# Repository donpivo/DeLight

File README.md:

Description: https://retronics.no/2024/05/17/diy-work-light-warning-light-emergency-light-morse-sos-flasher-for-dewalt-xr-batteries/

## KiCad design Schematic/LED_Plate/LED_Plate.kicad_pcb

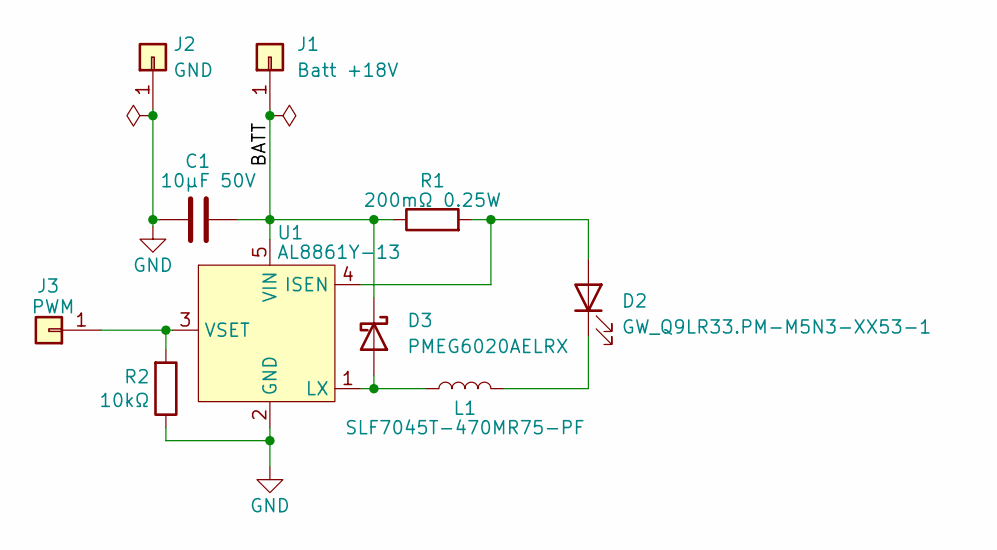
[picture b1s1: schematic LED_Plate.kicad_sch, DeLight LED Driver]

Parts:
C1: 10µF 50V; C_0805_2012Metric_Pad1.18x1.45mm_HandSolder
D2: GW_Q9LR33.PM-M5N3-XX53-1; LED_GW_Q9LR33.PM-M5N3-XX53-1
D3: PMEG6020AELRX; Nexperia_CFP3_SOD-123W
J1: Batt +18V; TestPoint_Pad_2.5x2.5mm
J2: GND; TestPoint_Pad_2.5x2.5mm
J3: PWM; TestPoint_Pad_2.5x2.5mm
L1: SLF7045T-470MR75-PF; SLF7032_7045
R1: 200mΩ 0.25W; R_1206_3216Metric_Pad1.30x1.75mm_HandSolder
R2: 10kΩ; R_0603_1608Metric_Pad0.98x0.95mm_HandSolder
U1: AL8861Y-13; SOT89-5

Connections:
/BATT: C1.2, D3.1 (K), J1.1, R1.1, U1.5 (VIN)
GND: C1.1, J2.1, R2.1, U1.2 (GND)
unnamed: D2.2 (A), R1.2, U1.4 (ISEN)
unnamed: D2.1 (K), L1.2
unnamed: D3.2 (A), L1.1, U1.1 (LX)
unnamed: J3.1, R2.2, U1.3 (VSET)

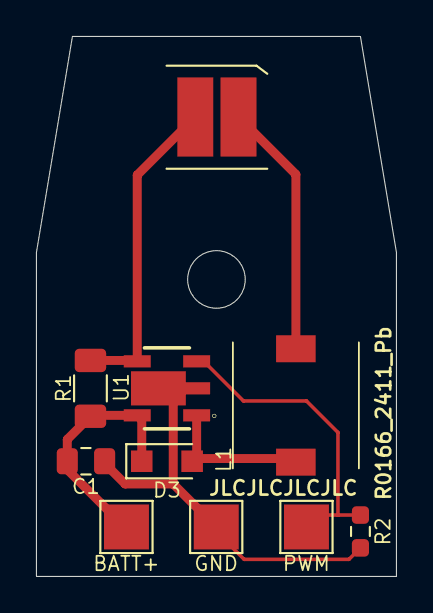
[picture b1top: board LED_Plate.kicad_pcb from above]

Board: 2 copper layers, 20.0 x 30.0 mm, 10 parts (0 on the bottom side), 6 nets.

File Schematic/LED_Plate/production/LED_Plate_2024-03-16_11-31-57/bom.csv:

Designator,Footprint,Quantity,Value,LCSC Part #
C1,0805,1,10µF,
D2,LED_GW_Q9LR33.PM-M5N3-XX53-1,1,LED,
D3,Nexperia_CFP3_SOD-123W,1,PMEG6020AELRX,
J1,TestPoint_Pad_2.5x2.5mm,1,Batt +18V,
J2,TestPoint_Pad_2.5x2.5mm,1,GND,
J3,TestPoint_Pad_2.5x2.5mm,1,PWM,
L1,SLF7032_7045,1,SLF7045T-470MR75-PF,
R1,1206,1,250mΩ 0.25W,
R2,0603,1,10kΩ,
U1,SOT89-5,1,AL8861Y-13,

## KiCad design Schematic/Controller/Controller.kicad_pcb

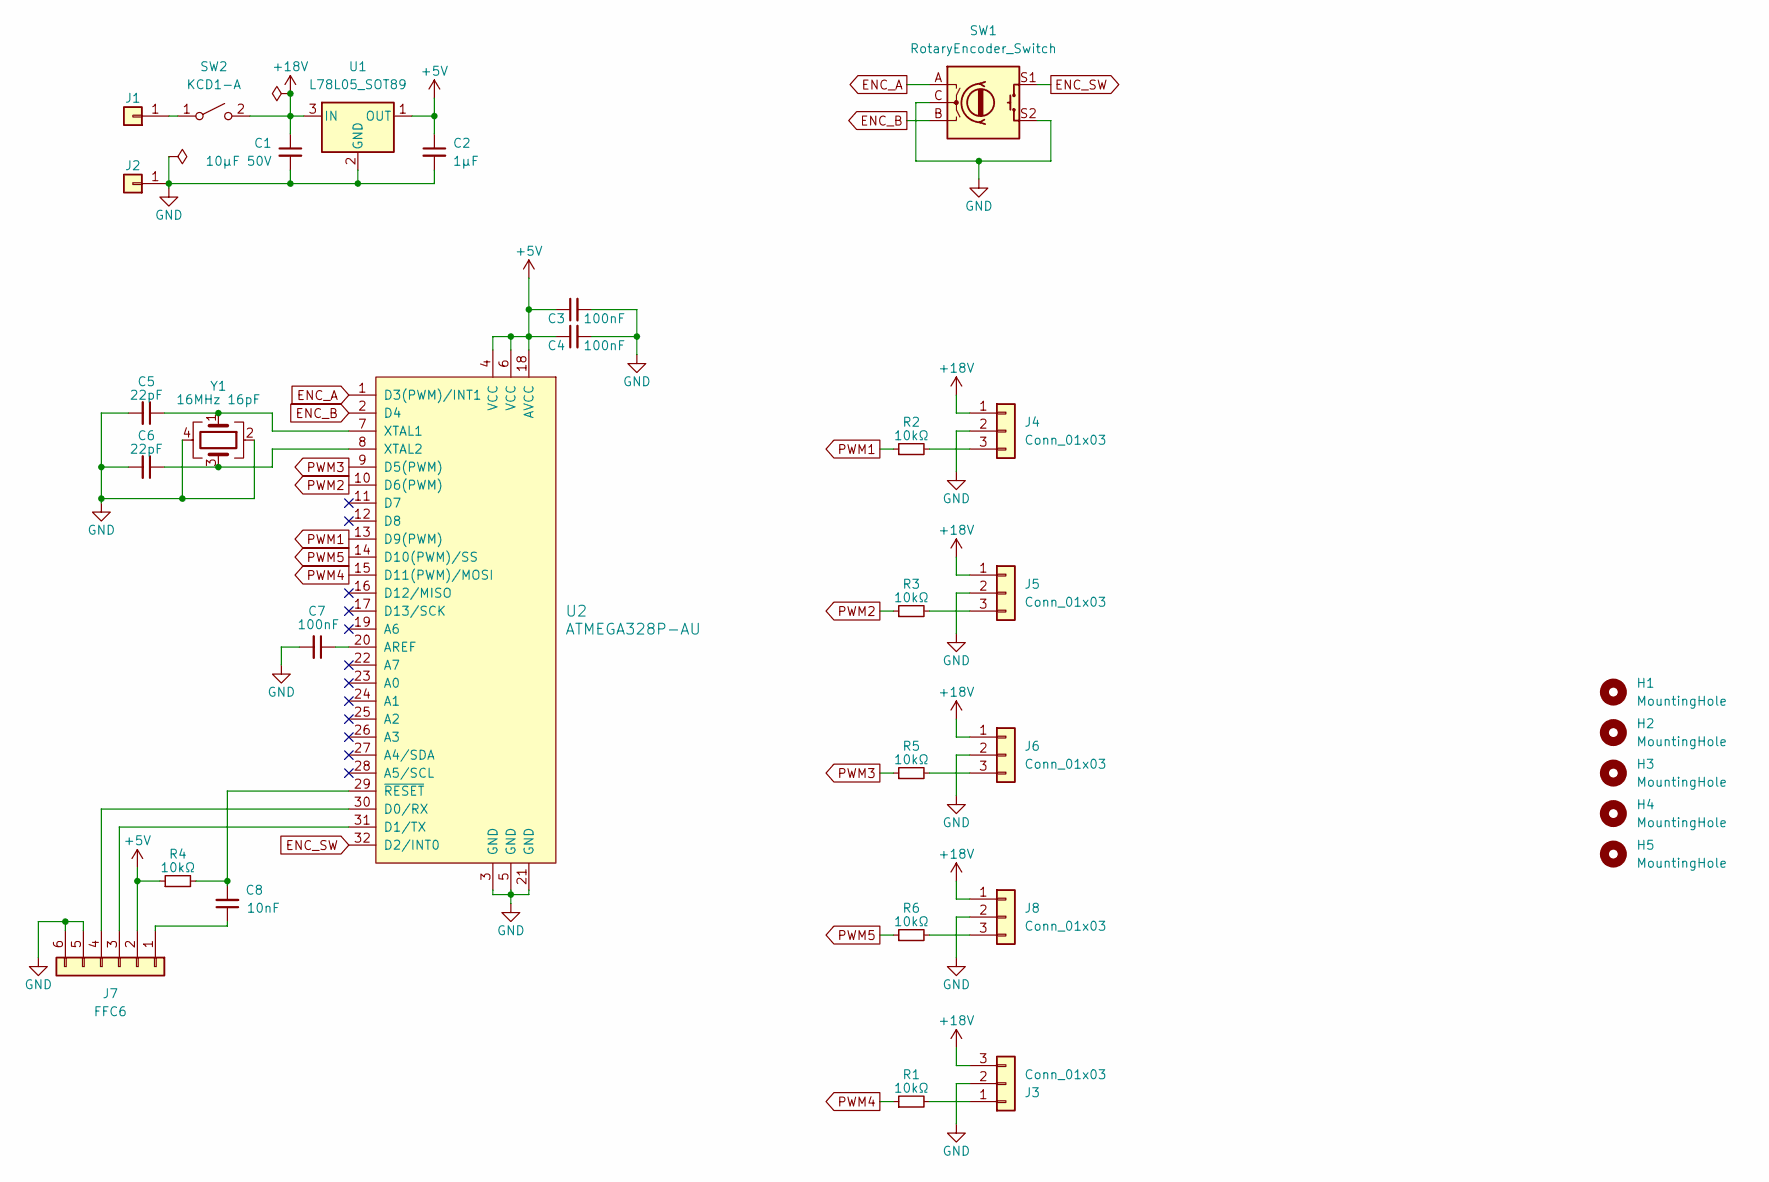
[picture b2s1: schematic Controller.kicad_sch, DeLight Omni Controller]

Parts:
C1: 10µF 50V; C_0805_2012Metric_Pad1.18x1.45mm_HandSolder
C2: 1µF; C_0805_2012Metric_Pad1.18x1.45mm_HandSolder
C3, C4, C7: 100nF; C_0603_1608Metric_Pad1.08x0.95mm_HandSolder
C5, C6: 22pF; C_0603_1608Metric_Pad1.08x0.95mm_HandSolder
C8: 10nF; C_0603_1608Metric_Pad1.08x0.95mm_HandSolder
H1, H2, H3, H4, H5: MountingHole; MountingHole_3.2mm_M3
J1, J2: Conn_01x01; TestPoint_THTPad_D3.0mm_Drill1.5mm
J3, J4, J5, J6, J8: Conn_01x03; Pads_3_2.5x2.5mm_5mmPitch
J7: FFC6; FFC_0527450697
R1, R2, R3, R4, R5, R6: 10kΩ; R_0603_1608Metric_Pad0.98x0.95mm_HandSolder
SW1: RotaryEncoder_Switch; PEC12R-2220F-S0024
SW2: KCD1-A; Pads_Dual_7x2mm_6.5mmPitch
U1: L78L05_SOT89; SOT-89-3
U2: ATMEGA328P-AU; TQFP-32_7x7mm_P0.8mm
Y1: 16MHz 16pF; Crystal_SMD_SeikoEpson_TSX3225-4Pin_3.2x2.5mm

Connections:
+5V: C2.1, C3.1, C4.1, J7.2, R4.1, U1.1 (OUT), U2.4 (VCC), U2.6 (VCC), U2.18 (AVCC)
+18V: C1.1, J3.3, J4.1, J5.1, J6.1, J8.1, SW2.2 (B), U1.3 (IN)
ENC_A: SW1.A, U2.1 (D3(PWM)/INT1)
ENC_B: SW1.B, U2.2 (D4)
ENC_SW: SW1.S1, U2.32 (D2/INT0)
GND: C1.2, C2.2, C3.2, C4.2, C5.2, C6.2, C7.2, J2.1, J3.2, J4.2, J5.2, J6.2, J7.5, J7.6, J8.2, SW1.C, SW1.S2, U1.2 (GND), U2.3 (GND), U2.5 (GND), U2.21 (GND), Y1.2, Y1.4
unnamed: J1.1, SW2.1 (A)
unnamed: J3.1, R1.2
unnamed: J4.3, R2.2
unnamed: J5.3, R3.2
unnamed: J6.3, R5.2
unnamed: C8.1, J7.1
unnamed: J7.3, U2.31 (D1/TX)
unnamed: J7.4, U2.30 (D0/RX)
unnamed: J8.3, R6.2
unnamed: C7.1, U2.20 (AREF)
unnamed: C5.1, U2.7 (XTAL1), Y1.1
unnamed: C6.1, U2.8 (XTAL2), Y1.3
unnamed: C8.2, R4.2, U2.29 (~RESET)
PWM1: R2.1, U2.13 (D9(PWM))
PWM2: R3.1, U2.10 (D6(PWM))
PWM3: R5.1, U2.9 (D5(PWM))
PWM4: R1.1, U2.15 (D11(PWM)/MOSI)
PWM5: R6.1, U2.14 (D10(PWM)/SS)

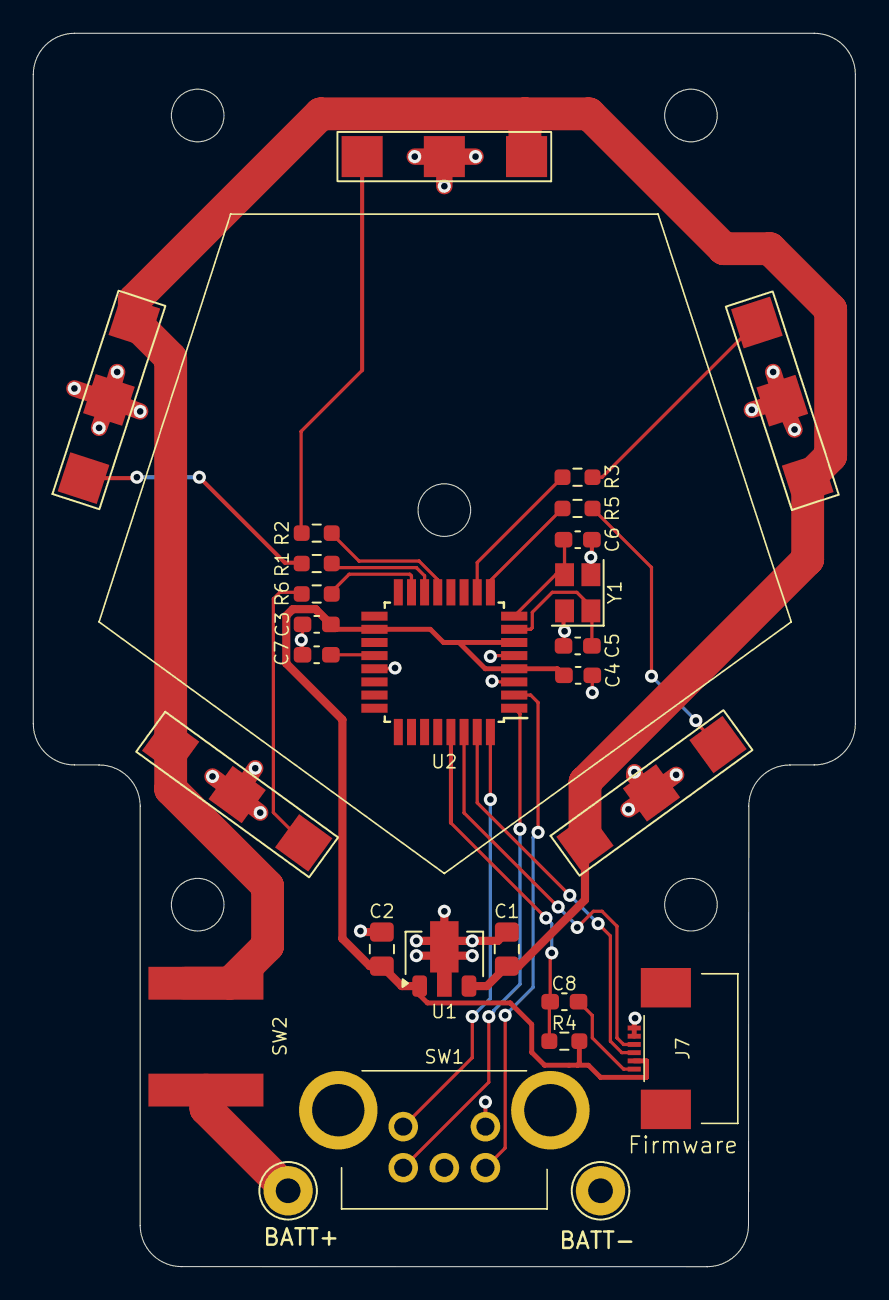
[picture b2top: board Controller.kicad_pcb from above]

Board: 2 copper layers, 50.0 x 75.0 mm, 32 parts (0 on the bottom side), 24 nets.

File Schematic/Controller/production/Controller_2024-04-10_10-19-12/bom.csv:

Designator,Footprint,Quantity,Value,LCSC Part #
C1,0805,1,10µF 50V,
C2,0805,1,1µF,
"C3, C4, C7",0603,3,100nF,
"C5, C6",0603,2,22pF,
C8,0603,1,10nF,
"H1, H2, H3, H4, H5",MountingHole_3.2mm_M3,5,MountingHole,
"J1, J2",TestPoint_THTPad_D3.0mm_Drill1.5mm,2,Conn_01x01,
"J3, J4, J5, J6, J8",Pads_3_2.5x2.5mm_5mmPitch,5,Conn_01x03,
J7,FFC_0527450697,1,FFC6,
"R1, R2, R3, R4, R5, R6",0603,6,10kΩ,
SW1,PEC12R-2220F-S0024,1,RotaryEncoder_Switch,
SW2,Pads_Dual_7x2mm_6.5mmPitch,1,KCD1-A,
U1,SOT-89-3,1,L78L05_SOT89,
U2,TQFP-32_7x7mm_P0.8mm,1,ATMEGA328P-AU,
Y1,Crystal_SMD_SeikoEpson_TSX3225-4Pin_3.2x2.5mm,1,16MHz 16pF,

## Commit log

2024-05-17 File cleanup
